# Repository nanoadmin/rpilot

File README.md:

# current placeholder for all rapsberry pilot work

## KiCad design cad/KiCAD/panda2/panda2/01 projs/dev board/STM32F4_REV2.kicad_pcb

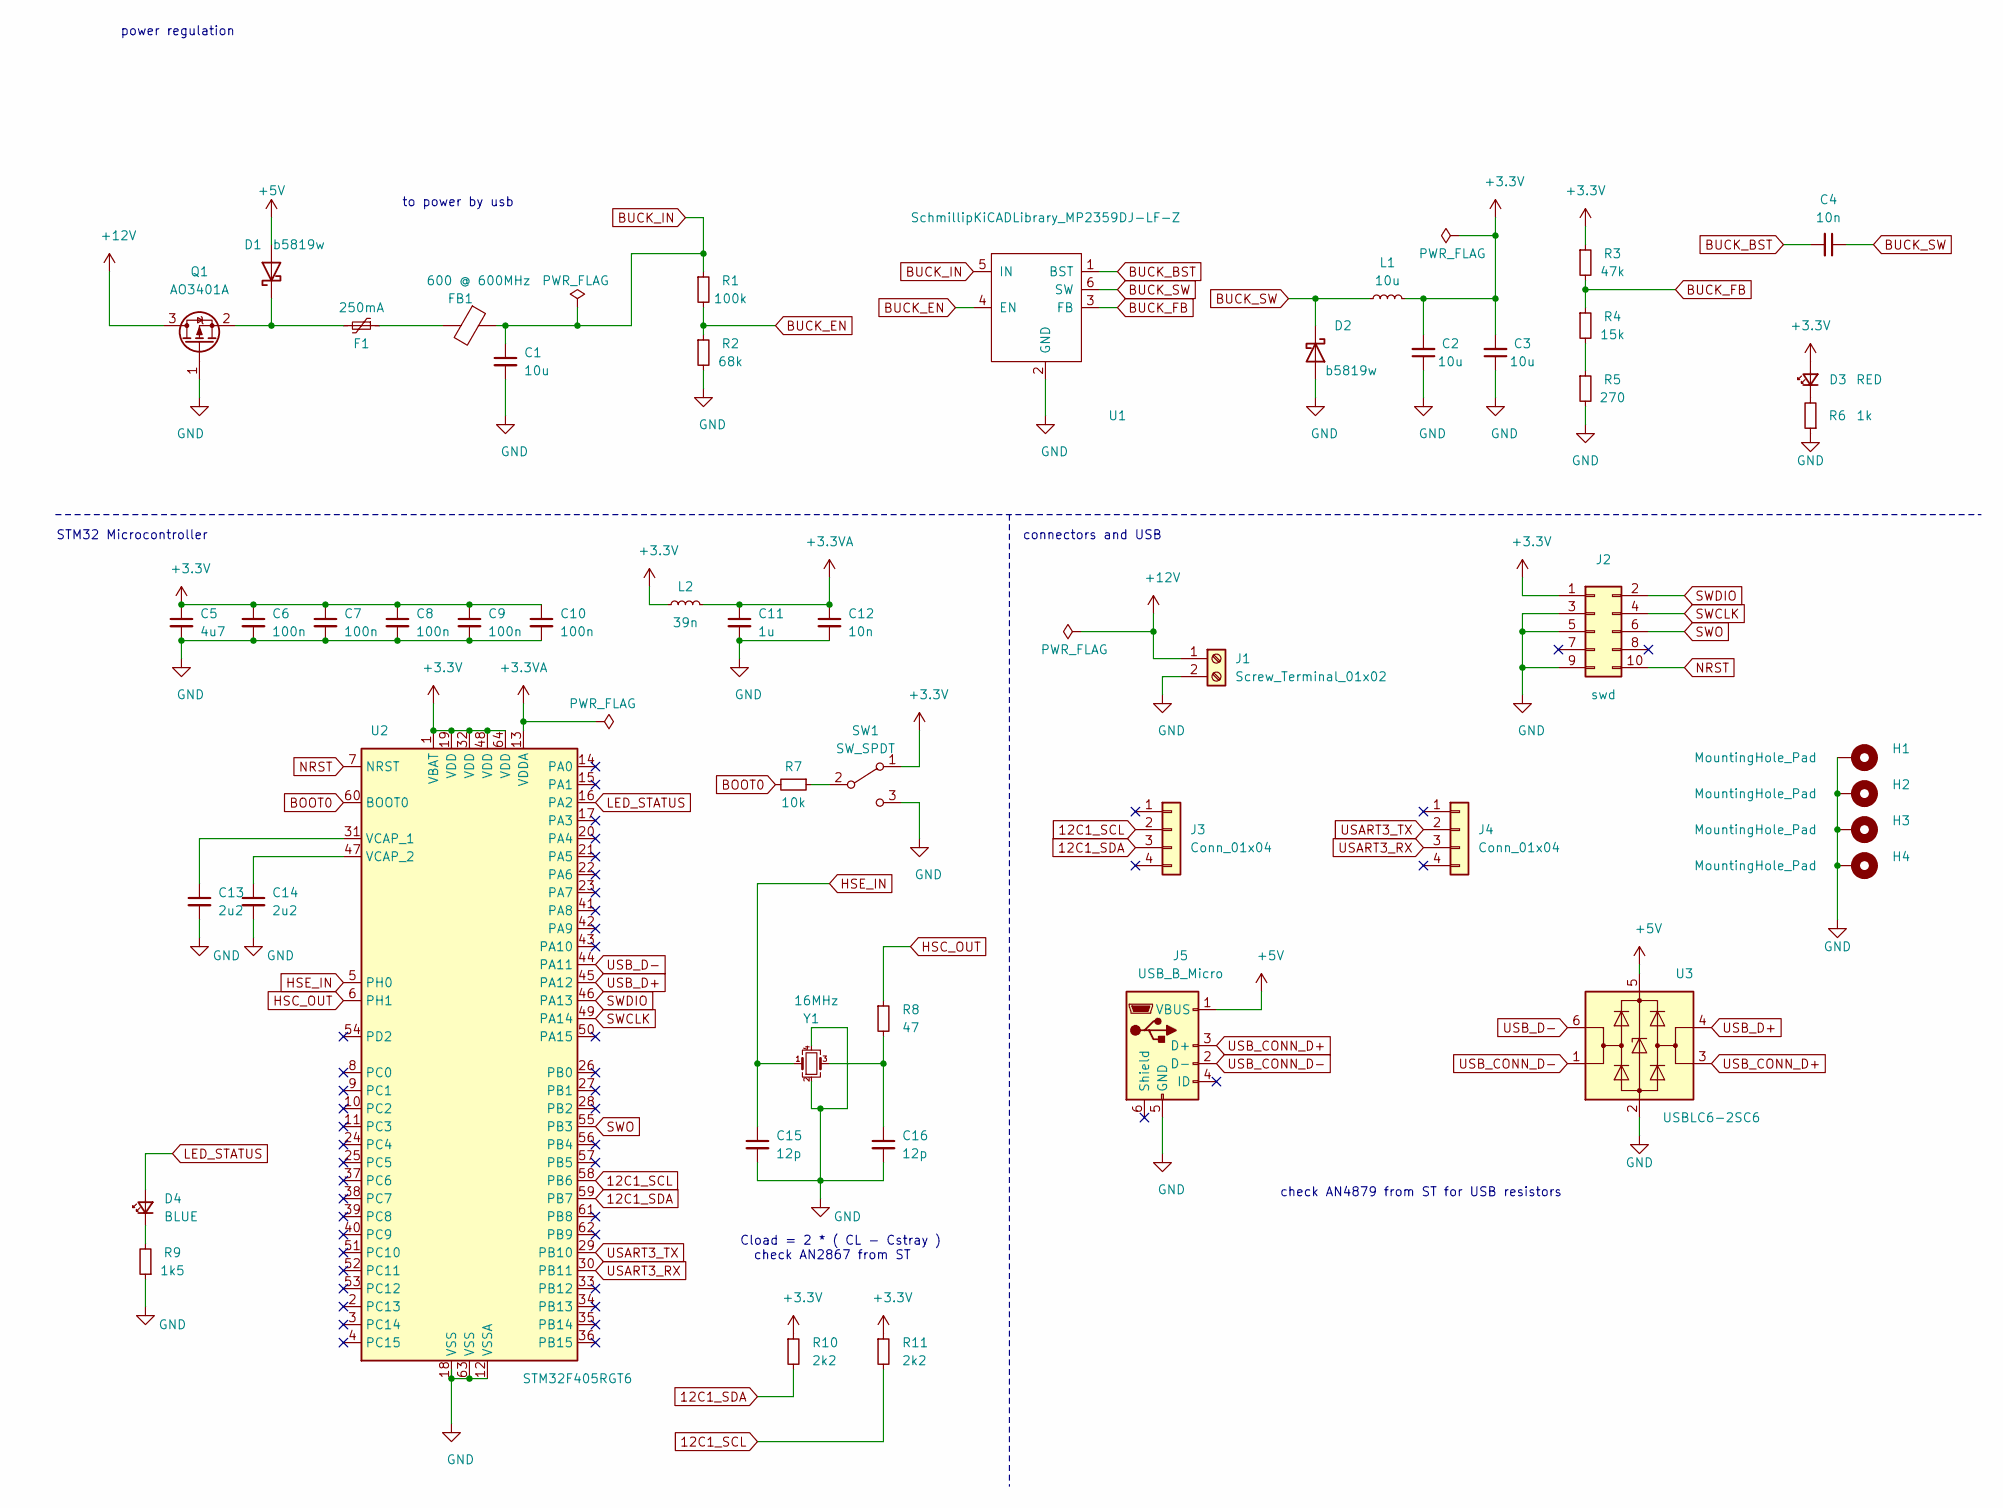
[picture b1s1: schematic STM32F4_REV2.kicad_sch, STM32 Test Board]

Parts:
C1, C2, C3: 10u; C_1206_3216Metric; LCSC Part # C13585
C4, C12: 10n; C_0603_1608Metric; LCSC Part # C57112
C5: 4u7; C_0603_1608Metric; LCSC Part # C19666
C6, C7, C8, C9, C10: 100n; C_0402_1005Metric; LCSC Part # C1525
C11: 1u; C_0603_1608Metric; LCSC Part # C15849
C13, C14: 2u2; C_0603_1608Metric; LCSC Part # C23630
C15, C16: 12p; C_0402_1005Metric; LCSC Part # C1547
D1, D2: b5819w; D_SOD-123; LCSC Part # C8598
D3: RED; LED_0603_1608Metric; LCSC Part # C72038
D4: BLUE; LED_0603_1608Metric; LCSC Part # C72041
F1: 250mA; Fuse_1206_3216Metric; LCSC Part # C369159
FB1: 600 @ 600MHz; L_0805_2012Metric; LCSC Part # C1017
H1, H2, H3, H4: MountingHole_Pad; MountingHole_4.3mm_M4_Pad_Via
J1: Screw_Terminal_01x02; TerminalBlock_Phoenix_PT-1,5-2-3.5-H_1x02_P3.50mm_Horizontal
J2: swd; PinHeader_2x05_P1.27mm_Vertical_SMD
J3, J4: Conn_01x04; Molex_PicoBlade_53048-0410_1x04_P1.25mm_Horizontal
J5: USB_B_Micro; USB_Micro-B_Amphenol_10103594-0001LF_Horizontal
L1: 10u; L_Sunlord_MWSA0518_5.4x5.2mm; LCSC Part # C408412
L2: 39n; L_0402_1005Metric; LCSC Part # C26443
Q1: AO3401A; SOT-23; LCSC Part # C15127
R1: 100k; R_0603_1608Metric; LCSC Part # C25803
R2: 68k; R_0603_1608Metric; LCSC Part # C23231
R3: 47k; R_0603_1608Metric; LCSC Part # C25819
R4: 15k; R_0603_1608Metric; LCSC Part # C22809
R5: 270; R_0603_1608Metric; LCSC Part # C22966
R6: 1k; R_0603_1608Metric; LCSC Part # C21190
R7: 10k; R_0402_1005Metric; LCSC Part # C25744
R8: 47; R_0402_1005Metric; LCSC Part # C25118
R9: 1k5; R_0603_1608Metric; LCSC Part # C22843
R10, R11: 2k2; R_0402_1005Metric; LCSC Part # C25879
SW1: SW_SPDT; SW_SPDT_PCM12
U1: SchmillipKiCADLibrary_MP2359DJ-LF-Z; SOT-23-6; LCSC Part # C14259
U2: STM32F405RGT6; LQFP-64_10x10mm_P0.5mm; LCSC Part # C15742
U3: USBLC6-2SC6; SOT-23-6; LCSC Part # C7519
Y1: 16MHz; Crystal_SMD_3225-4Pin_3.2x2.5mm; LCSC Part # C13738

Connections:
12C1_SCL: J3.2, R11.2, U2.58 (PB6)
12C1_SDA: J3.3, R10.2, U2.59 (PB7)
+3.3VA: C11.1, C12.1, L2.2, U2.13 (VDDA)
+3V3: C2.2, C3.2, C5.1, C6.1, C7.1, C8.1, C9.1, C10.1, D3.2 (A), J2.1, L1.2, L2.1, R3.1, R10.1, R11.1, SW1.1 (A), U2.1 (VBAT), U2.19 (VDD), U2.32 (VDD), U2.48 (VDD), U2.64 (VDD)
+5V: D1.2 (A), J5.1 (VBUS), U3.5 (VBUS)
+12V: J1.1, Q1.3 (D)
BOOT0: R7.2, U2.60 (BOOT0)
BUCK_BST: C4.2, U1.1 (BST)
BUCK_EN: R1.2, R2.1, U1.4 (EN)
BUCK_FB: R3.2, R4.1, U1.3 (FB)
BUCK_IN: C1.1, FB1.1, R1.1, U1.5 (IN)
BUCK_SW: C4.1, D2.1 (K), L1.1, U1.6 (SW)
GND: C1.2, C2.1, C3.1, C5.2, C6.2, C7.2, C8.2, C9.2, C10.2, C11.2, C12.2, C13.2, C14.2, C15.2, C16.2, D2.2 (A), H1.1, H2.1, H3.1, H4.1, J1.2, J2.3, J2.5, J2.9, J5.5 (GND), Q1.1 (G), R2.2, R5.2, R6.1, R9.1, SW1.3 (C), U1.2 (GND), U2.12 (VSSA), U2.18 (VSS), U2.63 (VSS), U3.2 (GND), Y1.2, Y1.4
HSC_OUT: R8.1, U2.6 (PH1)
HSE_IN: C15.1, U2.5 (PH0), Y1.1
LED_STATUS: D4.2 (A), U2.16 (PA2)
NRST: J2.10, U2.7 (NRST)
unnamed: C13.1, U2.31 (VCAP_1)
unnamed: C14.1, U2.47 (VCAP_2)
unnamed: C16.1, R8.2, Y1.3
unnamed: D1.1 (K), F1.2, Q1.2 (S)
unnamed: D3.1 (K), R6.2
unnamed: D4.1 (K), R9.2
unnamed: F1.1, FB1.2
unnamed: R4.2, R5.1
unnamed: R7.1, SW1.2 (B)
SWCLK: J2.4, U2.49 (PA14)
SWDIO: J2.2, U2.46 (PA13)
SWO: J2.6, U2.55 (PB3)
USART3_RX: J4.3, U2.30 (PB11)
USART3_TX: J4.2, U2.29 (PB10)
USB_CONN_D+: J5.3 (D+), U3.3 (I/O2)
USB_CONN_D-: J5.2 (D-), U3.1 (I/O1)
USB_D+: U2.45 (PA12), U3.4 (I/O2)
USB_D-: U2.44 (PA11), U3.6 (I/O1)
no_connect_36: J2.7
no_connect_37: J2.8
no_connect_38: J3.1
no_connect_39: J3.4
no_connect_40: J4.1
no_connect_41: J4.4
no_connect_42: J5.4 (ID)
no_connect_43: J5.6 (Shield)
no_connect_44: U2.10 (PC2)
no_connect_45: U2.11 (PC3)
no_connect_46: U2.14 (PA0)
no_connect_47: U2.15 (PA1)
no_connect_48: U2.17 (PA3)
no_connect_49: U2.2 (PC13)
no_connect_50: U2.20 (PA4)
no_connect_51: U2.21 (PA5)
no_connect_52: U2.22 (PA6)
no_connect_53: U2.23 (PA7)
no_connect_54: U2.24 (PC4)
no_connect_55: U2.25 (PC5)
no_connect_56: U2.26 (PB0)
no_connect_57: U2.27 (PB1)
no_connect_58: U2.28 (PB2)
no_connect_59: U2.3 (PC14)
no_connect_60: U2.33 (PB12)
no_connect_61: U2.34 (PB13)
no_connect_62: U2.35 (PB14)
no_connect_63: U2.36 (PB15)
no_connect_64: U2.37 (PC6)
no_connect_65: U2.38 (PC7)
no_connect_66: U2.39 (PC8)
no_connect_67: U2.4 (PC15)
no_connect_68: U2.40 (PC9)
no_connect_69: U2.41 (PA8)
no_connect_70: U2.42 (PA9)
no_connect_71: U2.43 (PA10)
no_connect_72: U2.50 (PA15)
no_connect_73: U2.51 (PC10)
no_connect_74: U2.52 (PC11)
no_connect_75: U2.53 (PC12)
no_connect_76: U2.54 (PD2)
no_connect_77: U2.56 (PB4)
no_connect_78: U2.57 (PB5)
no_connect_79: U2.61 (PB8)
no_connect_80: U2.62 (PB9)
no_connect_81: U2.8 (PC0)
no_connect_82: U2.9 (PC1)

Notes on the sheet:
STM32 Microcontroller
power regulation
to power by usb
Cload = 2 * ( CL - Cstray ) check AN2867 from ST
connectors and USB
check AN4879 from ST for USB resistors

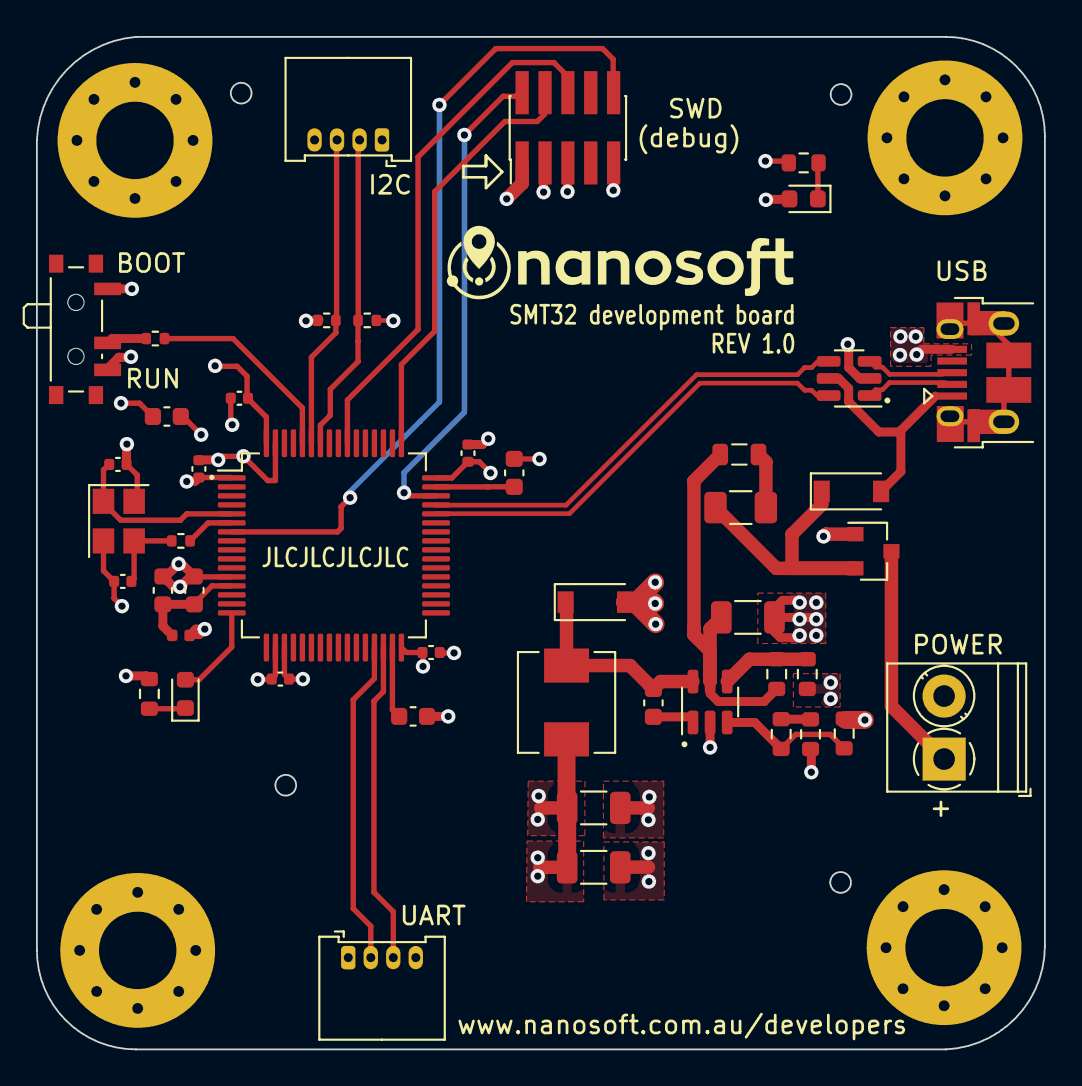
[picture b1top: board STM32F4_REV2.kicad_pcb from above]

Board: 4 copper layers, 56.0 x 56.3 mm, 50 parts (0 on the bottom side), 35 nets.

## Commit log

2020-10-09 Added wiring_overview
2020-10-09 Update wiring_overview
2020-11-23 Added open_ai_arch
2020-11-23 Update open_ai_arch
2020-11-25 Added pinouts
2020-11-25 Update pinouts
2020-12-15 moved files around
2020-12-15 deleted the copies of the images
2020-12-15 added spreadsheet
2020-12-15 organising files etc
2020-12-18 kicad files
2020-12-29 testdiagram.drawio
2020-12-29 Added test_image.svg
2020-12-29 Added cable_and_pinout.svg
2021-01-19 Added cable_and_pinout_2.svg
